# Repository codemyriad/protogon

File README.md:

# Protogon

The protogon is a prototyping board for the EMF Tildagon and Spaceagon badges.
If you don't understand what this means, it probably means that this project is not useful to you. But feel free to go down the rabbit hole!

* 64 kiB EEPROM
* EEPROM write protection jumper (P1) sort is write protected
* Qwiic connector
* I2c pull ups
* Power LED
* max 3v3 current: 600mA

It can be used to prototype a hexpansion. It features EEPROM (with write-protect jumper) and Qwiic connections.

The idea is based on JakeW's [protoboard hexpansion](https://www.tindie.com/products/jakew/protoboard-hexpansion/).

The board fits a 64 kbit EEPROM. There's a jumper you can short to write protect the EEPROM.
A connector is available to plug in Qwiic/STEMMA QT compatible sensors.

Even when not populated with components the board can be used for a basic hexpansion. The EEPROM is quite a valuable bit to mount, since the badge can recognize the hexpansion and load its code.

## Using files in the repo

The KiCad files are in the root: `codemyriad-protogon.kicad_*`.
The `fabrication/codemyriad-protogon-fab.zip` file is ready to upload to produce the board through a PCB manufacturing service. Make sure you select 1.0 mm FR4 and ENIG finish!
`fabrication/bom-lcsc.csv` contains a Bill Of Materials with LCSC codes.
`fabrication/gerbers/codemyriad-protogon-F_Paste.gtp` is the top solder paste layer, needed to order an SMT stencil (all SMD parts are on the top side, so only a top stencil is needed).

## Credits

* Many thanks to **JakeW** for the [Protoboard Hexpansion](https://www.tindie.com/products/jakew/protoboard-hexpansion/). The idea for this board came from seeing his one.
* **EMF Camp** for the badge, the hexpansion spec, and the [KiCad template](https://github.com/emfcamp/badge-2024-hardware). This work is based on those KiCad files.

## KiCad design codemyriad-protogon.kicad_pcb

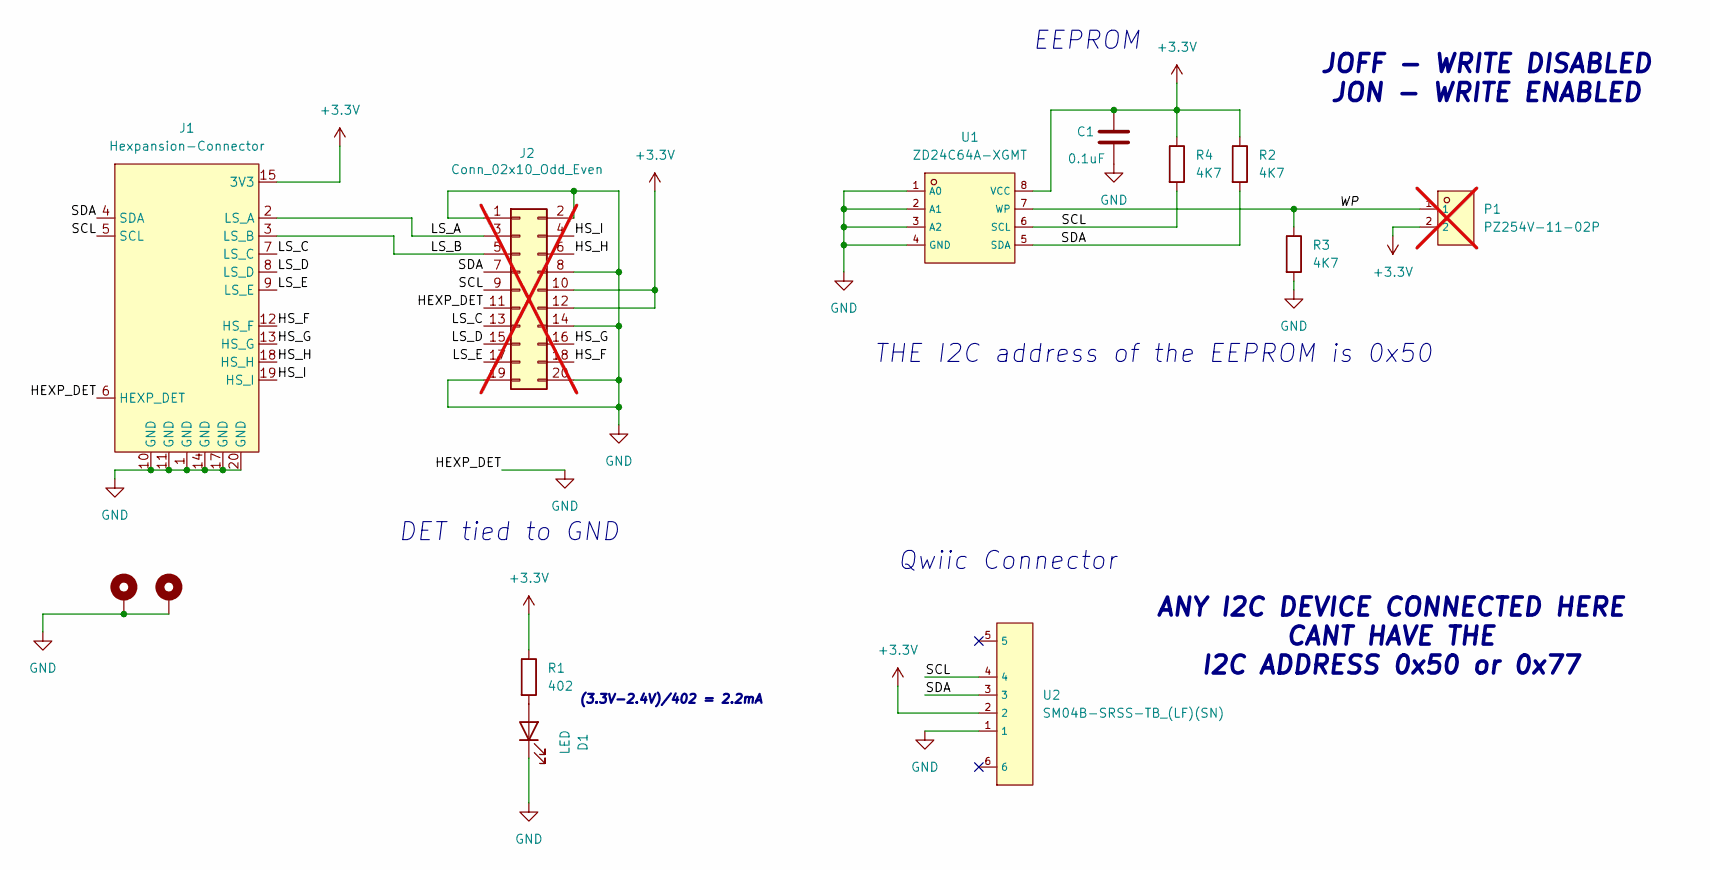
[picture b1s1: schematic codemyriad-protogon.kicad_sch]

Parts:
C1: 0.1uF; C_0603_1608Metric_Pad1.08x0.95mm_HandSolder; LCSC C1591
D1: LED; LED_0805_2012Metric; LCSC C19171391
H1, H2: MountingHole_Pad; MountingHole_2.2mm_M2_Pad_Via
J1: Hexpansion-Connector; hexpansion-edge-connector
J2: Conn_02x10_Odd_Even; PinHeader_2x10_P2.54mm_Vertical; LCSC C492427; not fitted
P1: PZ254V-11-02P; HDR-TH_2P-P2.54-V-M; LCSC C492401; not fitted
R1: 402; R_0603_1608Metric; LCSC C2930100
R2, R3, R4: 4K7; R_0603_1608Metric_Pad0.98x0.95mm_HandSolder; LCSC C105428
U1: ZD24C64A-XGMT; TSSOP-8_L4.4-W3.0-P0.65-LS6.4-BL; LCSC C2875852
U2: SM04B-SRSS-TB_(LF)(SN); CONN-SMD_4P-P1.00_SM04B-SRSS-TB-LF-SN; LCSC C160404

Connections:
+3.3V: C1.1, J1.15 (3V3), J1.16 (3V3), J2.10, J2.12, P1.2, R1.1, R2.1, R4.1, U1.8 (VCC), U2.2; also elsewhere on the board
/HS_F: J1.12 (HS_F), J2.18
/HS_G: J1.13 (HS_G), J2.16
/HS_H: J1.18 (HS_H), J2.6
/HS_I: J1.19 (HS_I), J2.4
/LS_A: J1.2 (LS_A), J2.3
/LS_B: J1.3 (LS_B), J2.5
/LS_C: J1.7 (LS_C), J2.13
/LS_D: J1.8 (LS_D), J2.15
/LS_E: J1.9 (LS_E), J2.17
/SCL: J1.5 (SCL), J2.9, R4.2, U1.6 (SCL), U2.4
/SDA: J1.4 (SDA), J2.7, R2.2, U1.5 (SDA), U2.3
/WP: P1.1, R3.1, U1.7 (WP)
GND: C1.2, D1.1 (K), H1.1, H2.1, J1.1 (GND), J1.6 (HEXP_DET), J1.10 (GND), J1.11 (GND), J1.14 (GND), J1.17 (GND), J1.20 (GND), J2.1, J2.2, J2.8, J2.11, J2.14, J2.19, J2.20, R3.2, U1.1 (A0), U1.2 (A1), U1.3 (A2), U1.4 (GND), U2.1; also elsewhere on the board
unnamed: D1.2 (A), R1.2

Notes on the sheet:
Qwiic Connector
(3.3V-2.4V)/402 = 2.2mA
DET tied to GND
EEPROM
JOFF - WRITE DISABLED JON - WRITE ENABLED
THE I2C address of the EEPROM is 0x50
ANY I2C DEVICE CONNECTED HERE CANT HAVE THE I2C ADDRESS 0x50 or 0x77

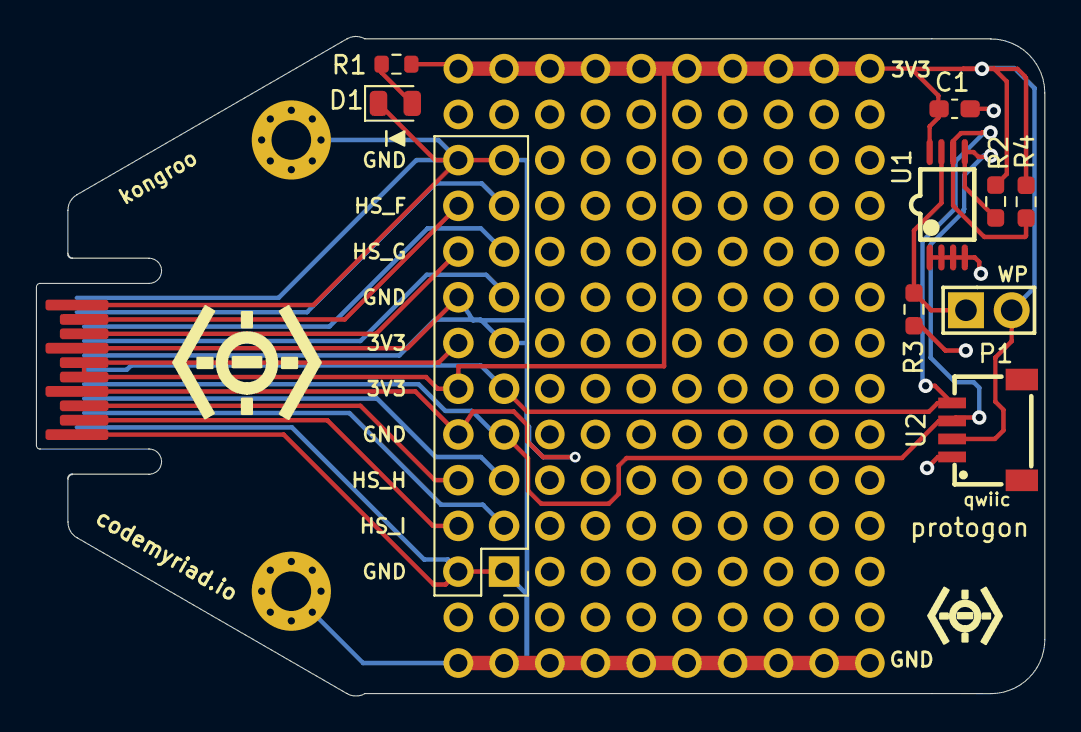
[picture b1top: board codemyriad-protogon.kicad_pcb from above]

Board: 2 copper layers, 56.0 x 36.6 mm, 14 parts (0 on the bottom side), 15 nets.

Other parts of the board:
PROTO1: integrated 10x14 protoboard grid

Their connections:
+3.3V: PROTO1.1, PROTO1.2, PROTO1.3, PROTO1.4, PROTO1.5, PROTO1.6, PROTO1.7, PROTO1.8, PROTO1.9, PROTO1.10; also elsewhere on the board
GND: PROTO1.111, PROTO1.112, PROTO1.113, PROTO1.114, PROTO1.115, PROTO1.116, PROTO1.117, PROTO1.118, PROTO1.119, PROTO1.120; also elsewhere on the board

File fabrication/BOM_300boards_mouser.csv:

Designator,Description,Footprint,Qty_per_board,Qty_needed_exact,Qty_to_order_with_spares,LCSC_Part,Manufacturer_Part,Manufacturer
C1,100nF (0.1uF) 50V X7R ceramic capacitor,0603,1,300,400,C1591,CL10B104KB8NNNC,Samsung Electro-Mechanics
D1,LED,0805,1,300,400,C19171391,,(generic - match to LCSC C19171391)
R1,402 ohm 1% resistor,0603,1,300,400,C2930100,FRC0603F4020TS,FOJAN
"R2,R3,R4",4.7k (4K7) 5% resistor,0603,3,900,1000,C105428,RC0603JR-074K7L,YAGEO
U1,EEPROM 64Kbit I2C,TSSOP-8,1,300,330,C2875852,ZD24C64A-XGMT,Zetta
U2,JST-SH 4-pin right-angle SMD connector (on 100 boards only),SM04B,1,100,120,C160404,SM04B-SRSS-TB(LF)(SN),JST

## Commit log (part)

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2026-06-22 Prepare for public release: keep internal notes and business docs out of the repo
    The hiring/recruitment material and supplier-cost research are internal; they are
    removed here and purged from history so the public repo is the open-hardware project
    only (design, tools, renders). Update READMEs accordingly.
2026-06-25 Simplify and add links
2026-06-25 qwiic-experiment: rewrite brief to be concise, expert-facing, and point at the base board
    README and REVIEW-HANDOFF were too verbose and spoke past experts. Rework both:
    - lead with the actual task: the LLM did a poor job placing the ear + EEPROM
    block; placing these well is the core ask
    - tell the reviewer up front to start from ../codemyriad-protogon.kicad_pcb
    (the trusted base board), not this folder's LLM attempt
    - add prominent links to the official hexpansion guide and badge-2024-hardware
2026-06-29 Final board with EEPROM and connector

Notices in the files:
codemyriad-protogon.kicad_pcb:
Based on EMF badge-2024-hardware hexpansion template, CERN-OHL-P-2.0
